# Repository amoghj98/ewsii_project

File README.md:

<h1><center><b>EWS-II Project Documentation</b><center></h1>
This is the documentation for the Project titled - "Applications of Colour Sensors" executed by the Amogh S. Joshi, Karan S. Agrawal and Shrihari S. Maheshwari in partial fulfillment of the requirements of the course "Electronics Workshop - II"
<h3>Contents :</h3> <ol>1. ewsii_proj <ol>1. lcd.h <br>2. lcd.cpp <br>3. coloursensor.h <br>4. coloursensor.cpp </ol>2. PCB files </ol>
<h3>ewsii_proj :</h3>
<h4>lcd.h :</h4> Contains the register definitions for the LCD screen as well as the class definition for the "lcd" class.
<h4>lcd.cpp :</h4> Contains the code for the functions contained within the "lcd" class. This file will ideally be unavailable to the user.
<h4>coloursensor.h :</h4> Contains the register definitions for the colour sensor as well as the class definition for the "clrsensor" class.
<h4>coloursensor.cpp :</h4> Contains the code for the functions contained within the "clrsensor" class. This file will ideally be unavailable to the user.
<h3>PCB  files :</h3> Contains the Eagle files for the project as well as the corresponding gerber files.

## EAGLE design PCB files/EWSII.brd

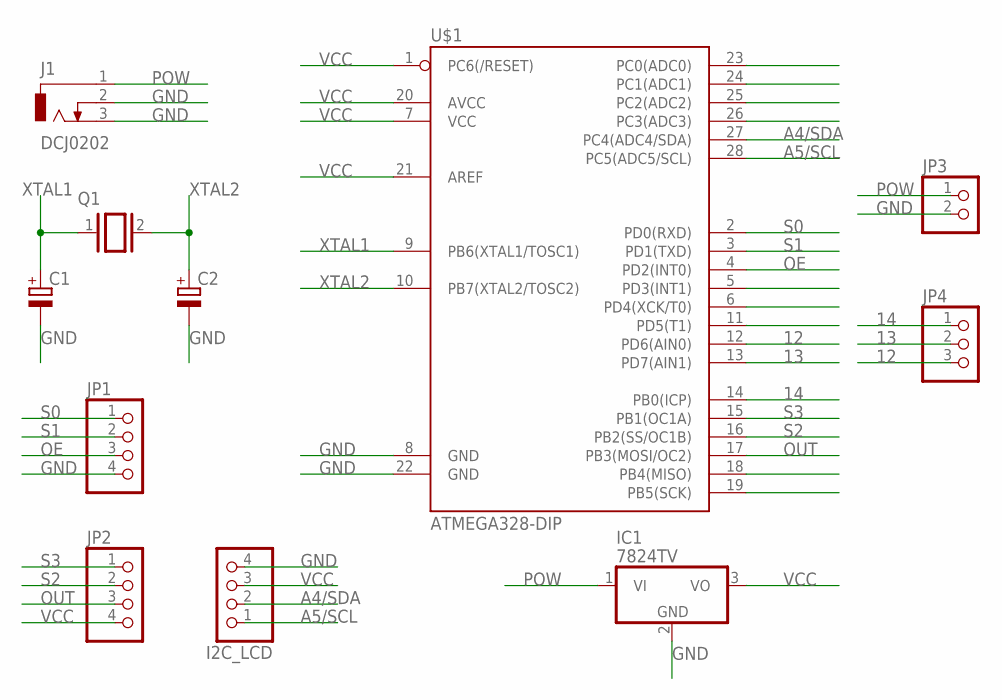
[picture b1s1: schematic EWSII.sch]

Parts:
C1, C2: CPOL-EUE2-5; E2-5
I2C_LCD: PINHD-1X4; 1X04
IC1: 7824TV; TO220V
J1: DCJ0202
JP1, JP2: PINHD-1X4; 1X04
JP3: PINHD-1X2; 1X02
JP4: PINHD-1X3; 1X03
Q1: XTAL/S; QS
U$1: ATMEGA328-DIP; DIP1016W53P254L3466H457Q28B

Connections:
12: JP4.3, U$1.12 (PD6(AIN0))
13: JP4.2, U$1.13 (PD7(AIN1))
14: JP4.1, U$1.14 (PB0(ICP))
A4/SDA: I2C_LCD.2, U$1.27 (PC4(ADC4/SDA))
A5/SCL: I2C_LCD.1, U$1.28 (PC5(ADC5/SCL))
GND: C1.-, C2.-, I2C_LCD.4, IC1.2 (GND), J1.2, J1.3, JP1.4, JP3.2, U$1.8 (GND), U$1.22 (GND)
OE: JP1.3, U$1.4 (PD2(INT0))
OUT: JP2.3, U$1.17 (PB3(MOSI/OC2))
POW: IC1.1 (VI), J1.1, JP3.1
S0: JP1.1, U$1.2 (PD0(RXD))
S1: JP1.2, U$1.3 (PD1(TXD))
S2: JP2.2, U$1.16 (PB2(SS/OC1B))
S3: JP2.1, U$1.15 (PB1(OC1A))
VCC: I2C_LCD.3, IC1.3 (VO), JP2.4, U$1.1 (PC6(/RESET)), U$1.7 (VCC), U$1.20 (AVCC), U$1.21 (AREF)
XTAL1: C1.+, Q1.1, U$1.9 (PB6(XTAL1/TOSC1))
XTAL2: C2.+, Q1.2, U$1.10 (PB7(XTAL2/TOSC2))

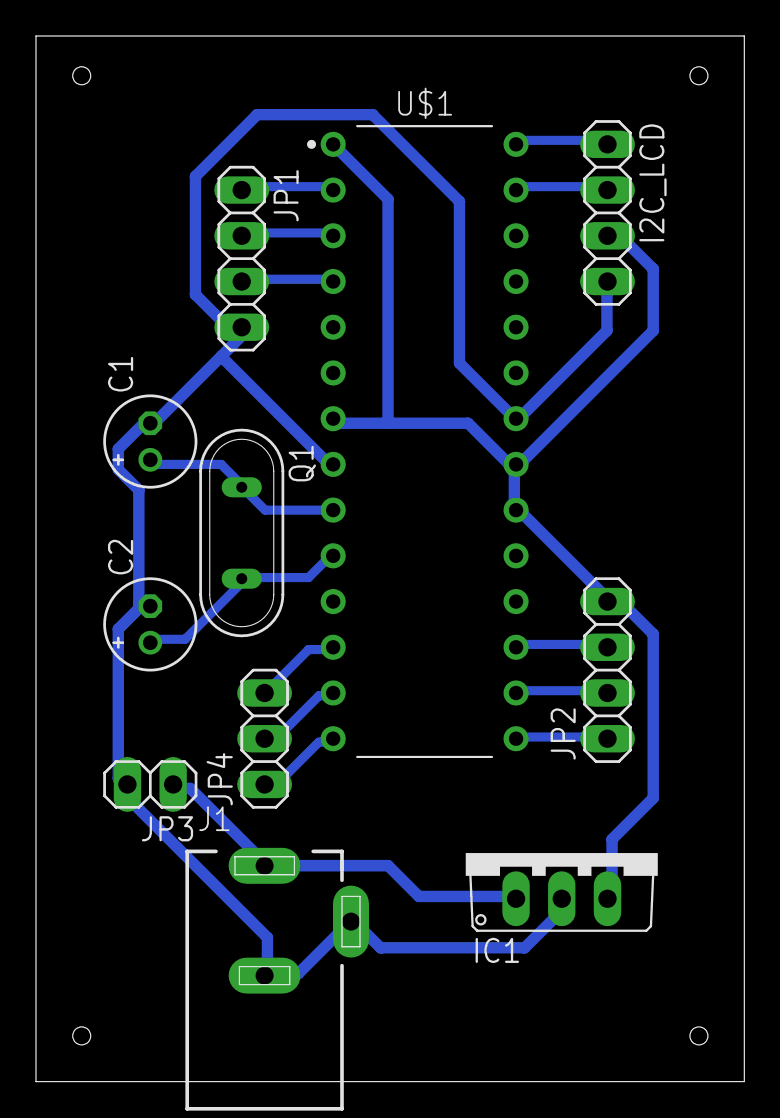
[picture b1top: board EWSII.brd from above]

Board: 2 copper layers, 39.4 x 58.1 mm, 11 parts (0 on the bottom side), 16 nets.

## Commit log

2019-03-05 add README
2019-03-05 add lcd code file skeleton
2019-03-13 add colour sensor code
2019-03-20 add lcd code
2019-03-20 minor changes to lcd
2019-03-21 aesthetic changes
2019-03-26 add PCB docs
2019-03-26 add pcb layout
2019-04-02 add printable docs
2019-05-07 final commit
